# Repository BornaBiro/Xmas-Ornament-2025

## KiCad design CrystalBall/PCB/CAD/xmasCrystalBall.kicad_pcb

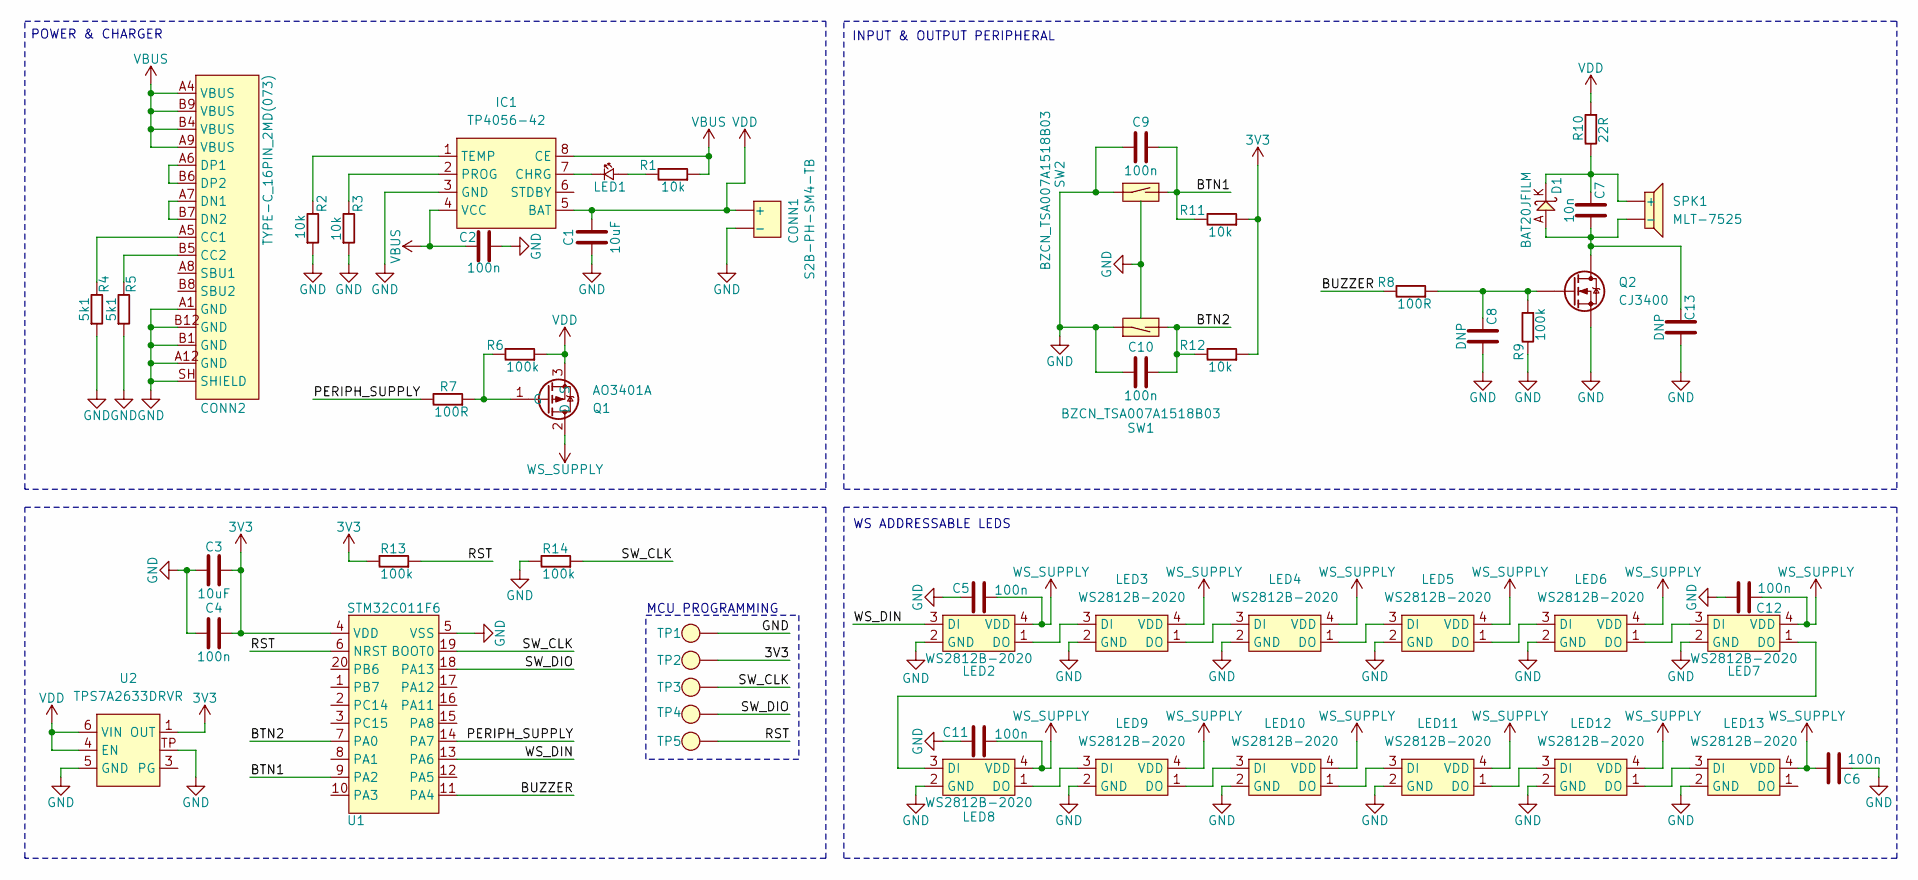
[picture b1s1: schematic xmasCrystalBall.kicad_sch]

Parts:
C1, C3: 10uF; C1206
C2, C4, C5, C6, C9, C10, C11, C12: 100n; C0603
C7: 10n; C0603
C8, C13: DNP; C0603
CONN1: S2B-PH-SM4-TB; JST_S2B-PH-SM4-TB
CONN2: TYPE-C_16PIN_2MD(073)
D1: BAT20JFILM; SOD323
IC1: TP4056-42; EMSOP
LED1: LED_0603
LED2, LED3, LED4, LED5, LED6, LED7, LED8, LED9, LED10, LED11, LED12, LED13: WS2812B-2020
Q1: AO3401A; SOT-23-3L
Q2: CJ3400; SOT-23-3L
R1, R2, R3, R11, R12: 10k; R0603
R4, R5: 5k1; R0603
R6, R9, R13, R14: 100k; R0603
R7, R8: 100R; R0603
R10: 22R; R0603
SPK1: MLT-7525; MTL-7525
SW1, SW2: BZCN_TSA007A1518B03; TSA007A1518B03
TP1, TP2, TP3, TP4, TP5: TP-1_5mm
U1: STM32C011F6; TSSOP20
U2: TPS7A2633DRVR; WSON-6

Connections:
3V3: C3.2, C4.2, R11.1, R12.1, R13.2, TP2.1 (TP), U1.4 (VDD), U2.1 (OUT)
/BTN1: C9.2, R11.2, SW2.2 (SW2), U1.9 (PA2)
/BTN2: C10.2, R12.2, SW1.2 (SW2), U1.7 (PA0)
/BUZZER: R8.2, U1.11 (PA4)
/PERIPH_SUPPLY: R7.2, U1.14 (PA7)
/RST: R13.1, TP5.1 (TP), U1.6 (NRST)
/SW_CLK: R14.1, TP3.1 (TP), U1.19 (BOOT0)
/SW_DIO: TP4.1 (TP), U1.18 (PA13)
/WS_DIN: LED2.3 (DI), U1.13 (PA6)
GND: C1.1, C2.1, C3.1, C4.1, C5.2, C6.2, C8.1, C9.1, C10.1, C11.2, C12.1, C13.1, CONN1.-, CONN2.A1 (GND), CONN2.A12 (GND), CONN2.B1 (GND), CONN2.B12 (GND), CONN2.SH (SHIELD), IC1.3 (GND), LED2.2 (GND), LED3.2 (GND), LED4.2 (GND), LED5.2 (GND), LED6.2 (GND), LED7.2 (GND), LED8.2 (GND), LED9.2 (GND), LED10.2 (GND), LED11.2 (GND), LED12.2 (GND), LED13.2 (GND), Q2.3 (S), R2.1, R3.1, R4.1, R5.1, R9.2, R14.2, SW1.1 (SW1), SW1.PAD, SW2.1 (SW1), SW2.PAD, TP1.1 (TP), U1.5 (VSS), U2.5 (GND), U2.TP
unnamed: C7.2, D1.K, R10.2, SPK1.+
unnamed: CONN2.A5 (CC1), R4.2
unnamed: CONN2.B5 (CC2), R5.2
unnamed: CONN2.A7 (DN1), CONN2.B7 (DN2)
unnamed: CONN2.A6 (DP1), CONN2.B6 (DP2)
unnamed: IC1.7 (CHRG), LED1.2 (K)
unnamed: IC1.2 (PROG), R3.2
unnamed: IC1.1 (TEMP), R2.2
unnamed: LED1.1 (A), R1.2
unnamed: LED2.1 (DO), LED3.3 (DI)
unnamed: LED3.1 (DO), LED4.3 (DI)
unnamed: LED4.1 (DO), LED5.3 (DI)
unnamed: LED5.1 (DO), LED6.3 (DI)
unnamed: LED6.1 (DO), LED7.3 (DI)
unnamed: LED7.1 (DO), LED8.3 (DI)
unnamed: LED8.1 (DO), LED9.3 (DI)
unnamed: LED9.1 (DO), LED10.3 (DI)
unnamed: LED10.1 (DO), LED11.3 (DI)
unnamed: LED11.1 (DO), LED12.3 (DI)
unnamed: LED12.1 (DO), LED13.3 (DI)
unnamed: Q1.1 (G), R6.2, R7.1
unnamed: C7.1, C13.2, D1.A, Q2.2 (D), SPK1.-
unnamed: C8.2, Q2.1 (G), R8.1, R9.1
VBUS: C2.2, CONN2.A4 (VBUS), CONN2.A9 (VBUS), CONN2.B4 (VBUS), CONN2.B9 (VBUS), IC1.4 (VCC), IC1.8 (CE), R1.1
VDD: C1.2, CONN1.+, IC1.5 (BAT), Q1.3 (S), R6.1, R10.1, U2.4 (EN), U2.6 (VIN)
WS_SUPPLY: C5.1, C6.1, C11.1, C12.2, LED2.4 (VDD), LED3.4 (VDD), LED4.4 (VDD), LED5.4 (VDD), LED6.4 (VDD), LED7.4 (VDD), LED8.4 (VDD), LED9.4 (VDD), LED10.4 (VDD), LED11.4 (VDD), LED12.4 (VDD), LED13.4 (VDD), Q1.2 (D)

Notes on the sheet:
INPUT & OUTPUT PERIPHERAL
POWER & CHARGER
WS ADDRESSABLE LEDS
MCU PROGRAMMING

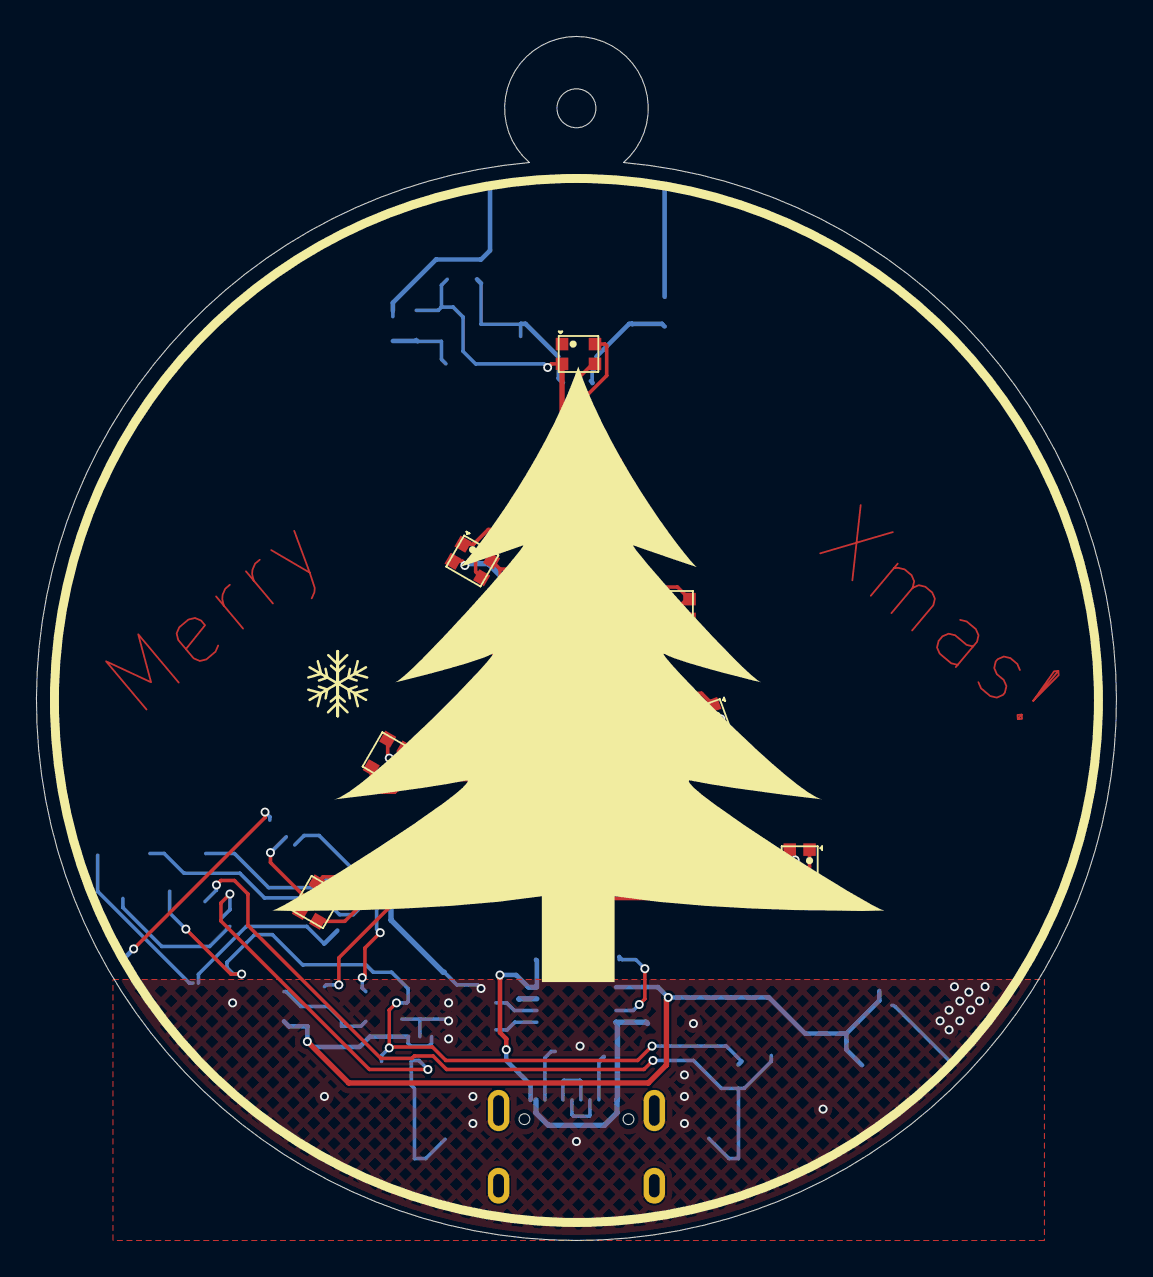
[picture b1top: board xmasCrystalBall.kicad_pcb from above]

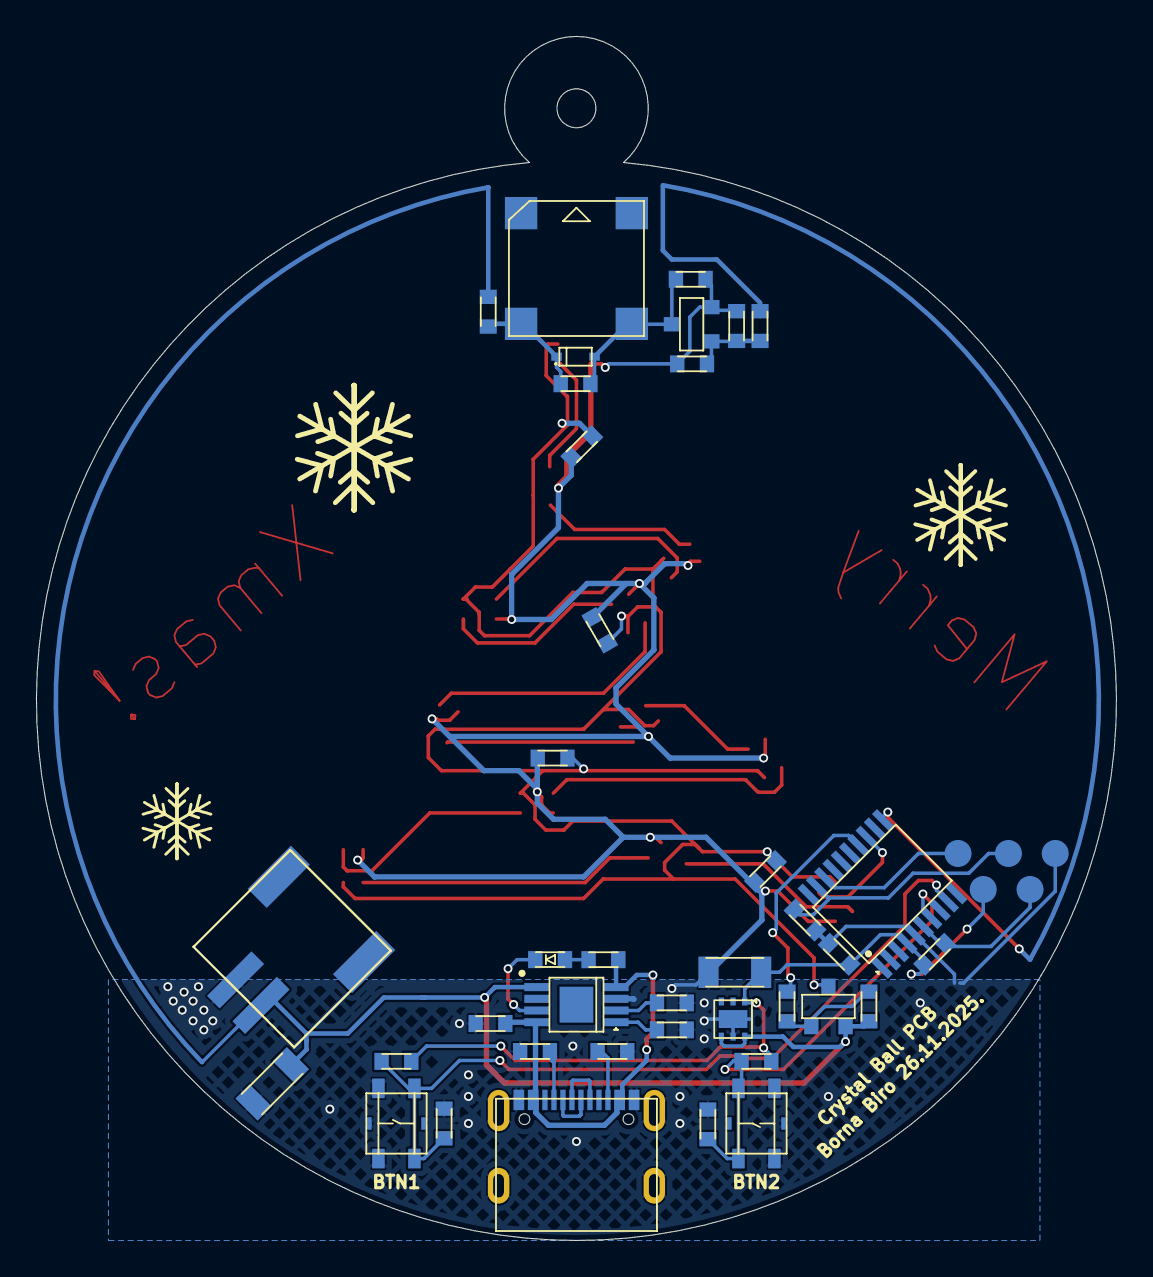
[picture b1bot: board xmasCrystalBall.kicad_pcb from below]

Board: 2 copper layers, 60.0 x 66.9 mm, 56 parts (44 on the bottom side), 36 nets.

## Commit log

2025-12-29 Added project files - transferred from my other repo.
2025-12-29 Some usable firmware written - but more for last year ornament than for this year.
